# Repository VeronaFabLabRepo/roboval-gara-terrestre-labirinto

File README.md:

# roboval-gara-terrestre-labirinto
tutti i firmware dei partecipanti alle gare di robotica terrestre Roboval "labirinto"

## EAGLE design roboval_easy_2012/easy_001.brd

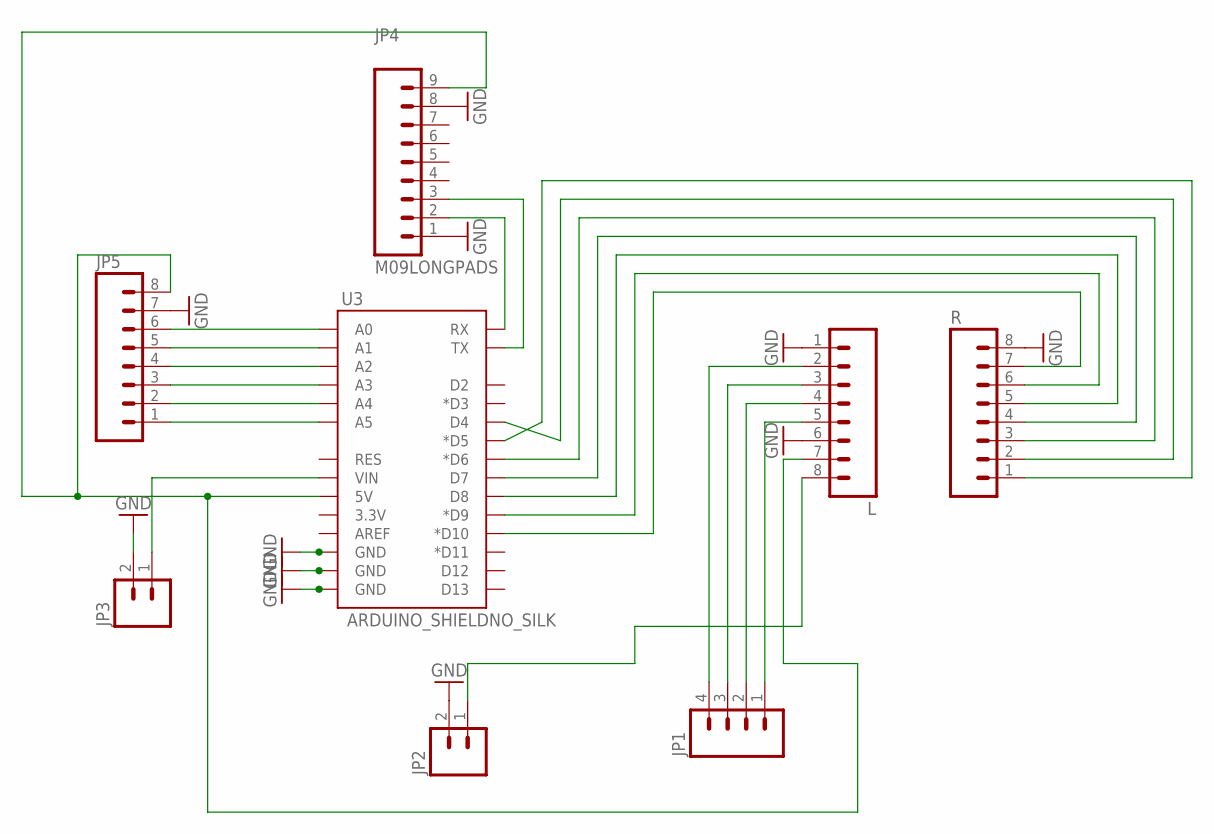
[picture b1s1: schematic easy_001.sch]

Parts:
JP1: M04LONGPADS; 1X04_LONGPADS
JP2, JP3: M02PTH3; 1X02_LONGPADS
JP4: M09LONGPADS; 1X09_LONGPADS
JP5: M08LONGPADS; 1X08_LONGPADS
L: M08LONGPADS; 1X08_LONGPADS
R: M08LONGPADS; 1X08_LONGPADS
U3: ARDUINO_SHIELDNO_SILK; DUEMILANOVE_VIAS

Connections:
GND: JP2.2, JP3.2, JP4.1, JP4.8, JP5.7, L.1, L.6, R.8, U3.GND@0 (GND), U3.GND@1 (GND), U3.GND@2 (GND)
unnamed: R.7, U3.D10 (*D10)
unnamed: R.6, U3.D9 (*D9)
unnamed: R.5, U3.D8
unnamed: R.4, U3.D7
unnamed: R.3, U3.D6 (*D6)
unnamed: R.2, U3.D4
unnamed: R.1, U3.D5 (*D5)
unnamed: JP1.4, L.2
unnamed: JP1.3, L.3
unnamed: JP1.2, L.4
unnamed: JP1.1, L.5
unnamed: JP4.9, JP5.8, L.7, U3.5V
unnamed: JP2.1, L.8
unnamed: JP5.1, U3.A5
unnamed: JP5.2, U3.A4
unnamed: JP5.3, U3.A3
unnamed: JP5.4, U3.A2
unnamed: JP5.5, U3.A1
unnamed: JP5.6, U3.A0
unnamed: JP3.1, U3.VIN
unnamed: JP4.2, U3.RX
unnamed: JP4.3, U3.TX

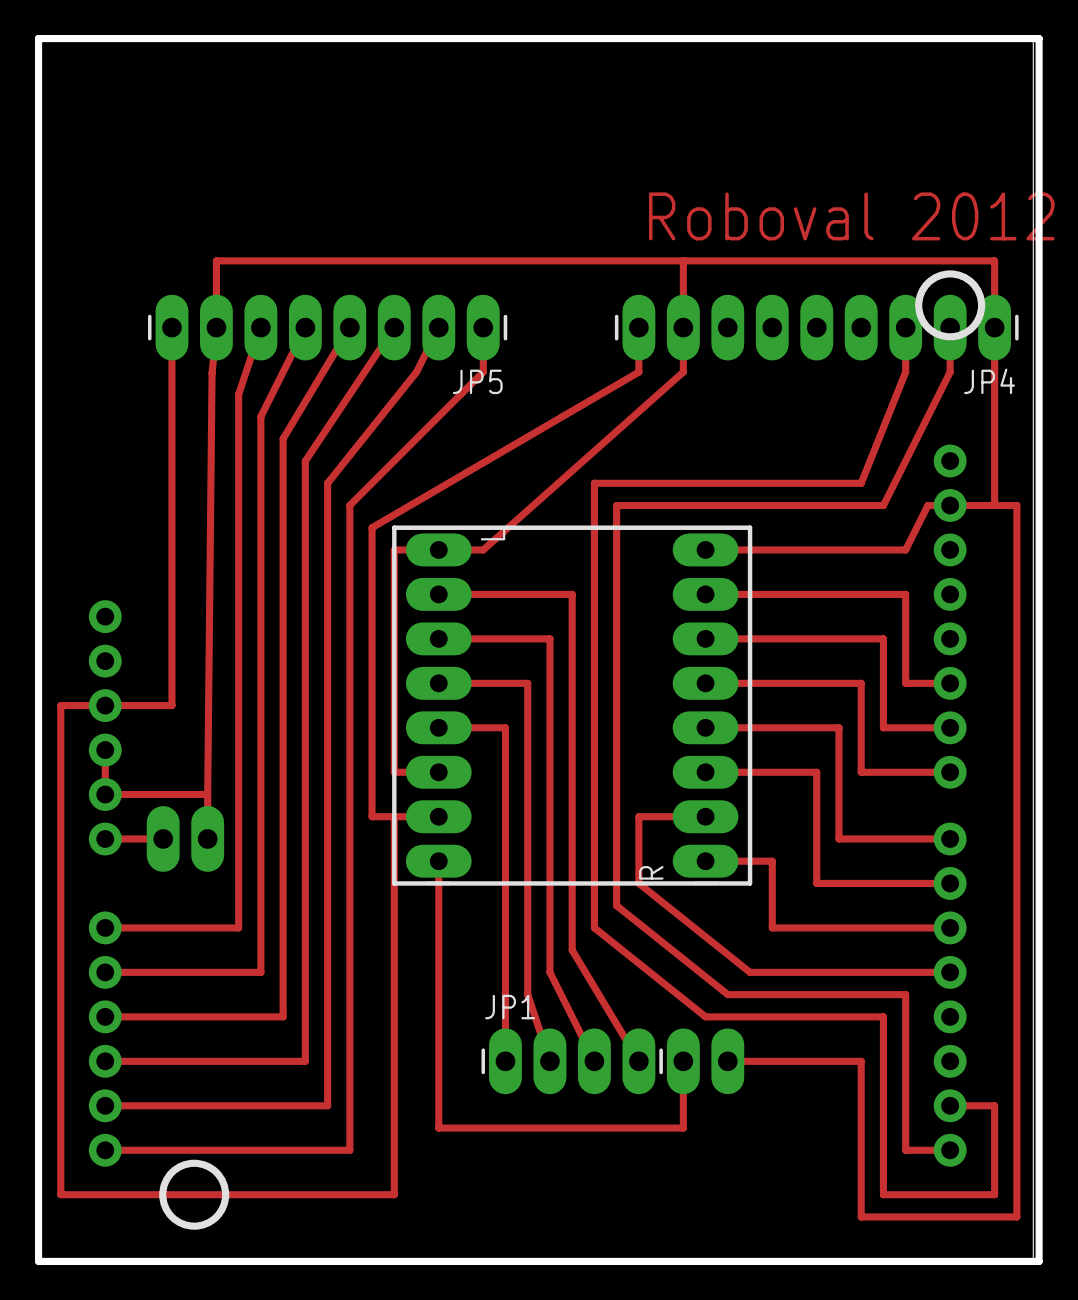
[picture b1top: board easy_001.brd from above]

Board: 2 copper layers, 57.1 x 69.9 mm, 8 parts (0 on the bottom side), 23 nets.

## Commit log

2015-03-19 sorgenti
2015-03-19 rimossi file generici
2015-06-10 firmware 2015
2016-05-31 aggiunti firmware 2016
2017-06-30 aggiunti file 2017

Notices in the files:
parts and their libraries:
SparkFun-Boards: Licensing: CC v3.0 Share-Alike You are welcome to use this library for commercial purposes.
